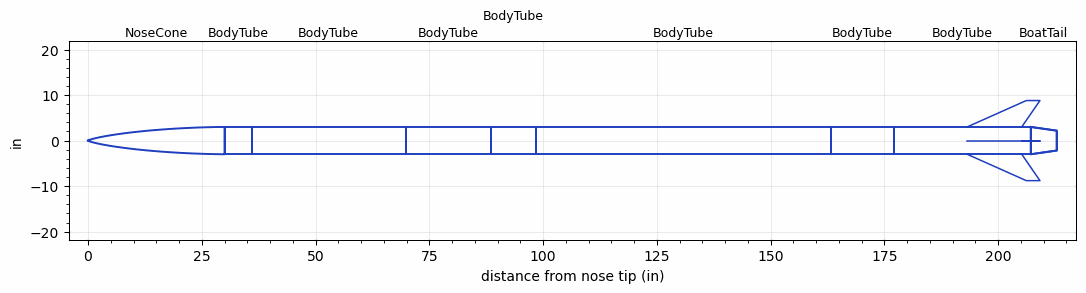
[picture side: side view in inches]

<RASAeroDocument>
 <FileVersion>2</FileVersion>
 <RocketDesign>
  <NoseCone>
   <Length>30</Length>
   <Diameter>6</Diameter>
   <Shape>LV-Haack</Shape>
   <Location>0</Location>
  </NoseCone>
  <BodyTube>
   <Length>6</Length>
   <Diameter>6</Diameter>
   <Location>30</Location>
  </BodyTube>
  <BodyTube>
   <Length>33.8</Length>
   <Diameter>6</Diameter>
   <Location>36</Location>
  </BodyTube>
  <BodyTube>
   <Length>18.7</Length>
   <Diameter>6</Diameter>
   <Location>69.8</Location>
  </BodyTube>
  <BodyTube>
   <Length>10</Length>
   <Diameter>6</Diameter>
   <Location>88.5</Location>
  </BodyTube>
  <BodyTube>
   <Length>64.69</Length>
   <Diameter>6</Diameter>
   <Location>98.5</Location>
  </BodyTube>
  <BodyTube>
   <Length>14</Length>
   <Diameter>6</Diameter>
   <Location>163.19</Location>
  </BodyTube>
  <BodyTube>
   <Length>30</Length>
   <Diameter>6</Diameter>
   <Location>177.19</Location>
   <BoattailLength>5.7</BoattailLength>
   <BoattailRearDiameter>4.36</BoattailRearDiameter>
   <Fin>
    <Count>4</Count>
    <Chord>12</Chord>
    <Span>5.8</Span>
    <SweepDistance>13</SweepDistance>
    <TipChord>3</TipChord>
    <Thickness>0.3</Thickness>
    <LERadius>0.01</LERadius>
    <Location>14</Location>
    <AirfoilSection>Hexagonal</AirfoilSection>
    <FX1>0.3</FX1>
    <FX3>0.3</FX3>
   </Fin>
  </BodyTube>
  <BoatTail>
   <Length>5.7</Length>
   <Diameter>6</Diameter>
   <RearDiameter>4.36</RearDiameter>
   <Location>207.19</Location>
  </BoatTail>
  <Surface>Camouflage Paint</Surface>
  <ModifiedBarrowman>True</ModifiedBarrowman>
  <Turbulence>True</Turbulence>
  <UseBooster1>False</UseBooster1>
  <UseBooster2>False</UseBooster2>
 </RocketDesign>
 <LaunchSite>
  <Altitude>2950</Altitude>
  <Pressure>27</Pressure>
  <RodAngle>8</RodAngle>
  <RodLength>32.8</RodLength>
  <Temperature>76</Temperature>
  <WindSpeed>18</WindSpeed>
 </LaunchSite>
 <Recovery>
  <Altitude1>1000</Altitude1>
  <Altitude2>1000</Altitude2>
  <DeviceType1>None</DeviceType1>
  <DeviceType2>None</DeviceType2>
  <Event1>False</Event1>
  <Event2>False</Event2>
  <Size1>1</Size1>
  <Size2>1</Size2>
  <EventType1>None</EventType1>
  <EventType2>None</EventType2>
  <CD1>1.33</CD1>
  <CD2>1.33</CD2>
 </Recovery>
 <SimulationList>
  <Simulation>
   <SustainerEngine>COMBINED_3_6  (TAMUSRT)</SustainerEngine>
   <SustainerLaunchWt>155</SustainerLaunchWt>
   <SustainerCG>134</SustainerCG>
   <SustainerIgnitionDelay>0</SustainerIgnitionDelay>
   <Booster1SeparationDelay>0</Booster1SeparationDelay>
   <Booster1IgnitionDelay>0</Booster1IgnitionDelay>
   <IncludeBooster1>False</IncludeBooster1>
   <Booster2Delay>0</Booster2Delay>
   <IncludeBooster2>False</IncludeBooster2>
   <TimetoApogee>44.7585</TimetoApogee>
   <MaxAltitude>29447.64</MaxAltitude>
   <MaxVelocity>1482.207</MaxVelocity>
  </Simulation>
  <Simulation>
   <SustainerEngine>COMB_PLUS  (TAMUSRT)</SustainerEngine>
   <SustainerLaunchWt>128</SustainerLaunchWt>
   <SustainerCG>125</SustainerCG>
   <SustainerIgnitionDelay>0</SustainerIgnitionDelay>
   <Booster1SeparationDelay>0</Booster1SeparationDelay>
   <Booster1IgnitionDelay>0</Booster1IgnitionDelay>
   <IncludeBooster1>False</IncludeBooster1>
   <Booster2Delay>0</Booster2Delay>
   <IncludeBooster2>False</IncludeBooster2>
   <TimetoApogee>41.71901</TimetoApogee>
   <MaxAltitude>26628.62</MaxAltitude>
   <MaxVelocity>1520.361</MaxVelocity>
  </Simulation>
  <Simulation>
   <SustainerEngine>COMBINED_30  (TAMUSRT)</SustainerEngine>
   <SustainerLaunchWt>149</SustainerLaunchWt>
   <SustainerCG>130</SustainerCG>
   <SustainerIgnitionDelay>0</SustainerIgnitionDelay>
   <Booster1SeparationDelay>0</Booster1SeparationDelay>
   <Booster1IgnitionDelay>0</Booster1IgnitionDelay>
   <IncludeBooster1>False</IncludeBooster1>
   <Booster2Delay>0</Booster2Delay>
   <IncludeBooster2>False</IncludeBooster2>
  </Simulation>
  <Simulation>
   <SustainerEngine>CUST  (TAMUSRT)</SustainerEngine>
   <SustainerLaunchWt>152</SustainerLaunchWt>
   <SustainerCG>132</SustainerCG>
   <SustainerIgnitionDelay>0</SustainerIgnitionDelay>
   <Booster1SeparationDelay>0</Booster1SeparationDelay>
   <Booster1IgnitionDelay>0</Booster1IgnitionDelay>
   <IncludeBooster1>False</IncludeBooster1>
   <Booster2Delay>0</Booster2Delay>
   <IncludeBooster2>False</IncludeBooster2>
   <TimetoApogee>45.99829</TimetoApogee>
   <MaxAltitude>31779.34</MaxAltitude>
   <MaxVelocity>1582.848</MaxVelocity>
  </Simulation>
  <Simulation>
   <SustainerEngine>TRIAL  (TAMUSRT)</SustainerEngine>
   <SustainerLaunchWt>155</SustainerLaunchWt>
   <SustainerCG>133</SustainerCG>
   <SustainerIgnitionDelay>0</SustainerIgnitionDelay>
   <Booster1SeparationDelay>0</Booster1SeparationDelay>
   <Booster1IgnitionDelay>0</Booster1IgnitionDelay>
   <IncludeBooster1>False</IncludeBooster1>
   <Booster2Delay>0</Booster2Delay>
   <IncludeBooster2>False</IncludeBooster2>
   <TimetoApogee>44.46854</TimetoApogee>
   <MaxAltitude>29170.6</MaxAltitude>
   <MaxVelocity>1529.231</MaxVelocity>
  </Simulation>
 </SimulationList>
</RASAeroDocument>
